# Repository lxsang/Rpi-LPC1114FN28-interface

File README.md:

# Rpi-LPC1114FN28-interface

This is a hobby project for an embedded application.  The point is that the Pi  is connected to a circuit based on the LPC1114FN28, in which, the ARM cortex M0 chip is used to collect sensor datas (IR sensor, sonar sensor, etc.) and control some motors using an IC controller. The Pi talks to the LPC1114FN28 via a serial connection (UART or SPI), and takes care of some high level calculations based on the datas provided by the LPC chip, it then can analyse the environment's context and send commands to the slave (ARM) chip for some control. For this prject, i decide to design my own PCB for the interface and write a firmware/middleware for  the interface.

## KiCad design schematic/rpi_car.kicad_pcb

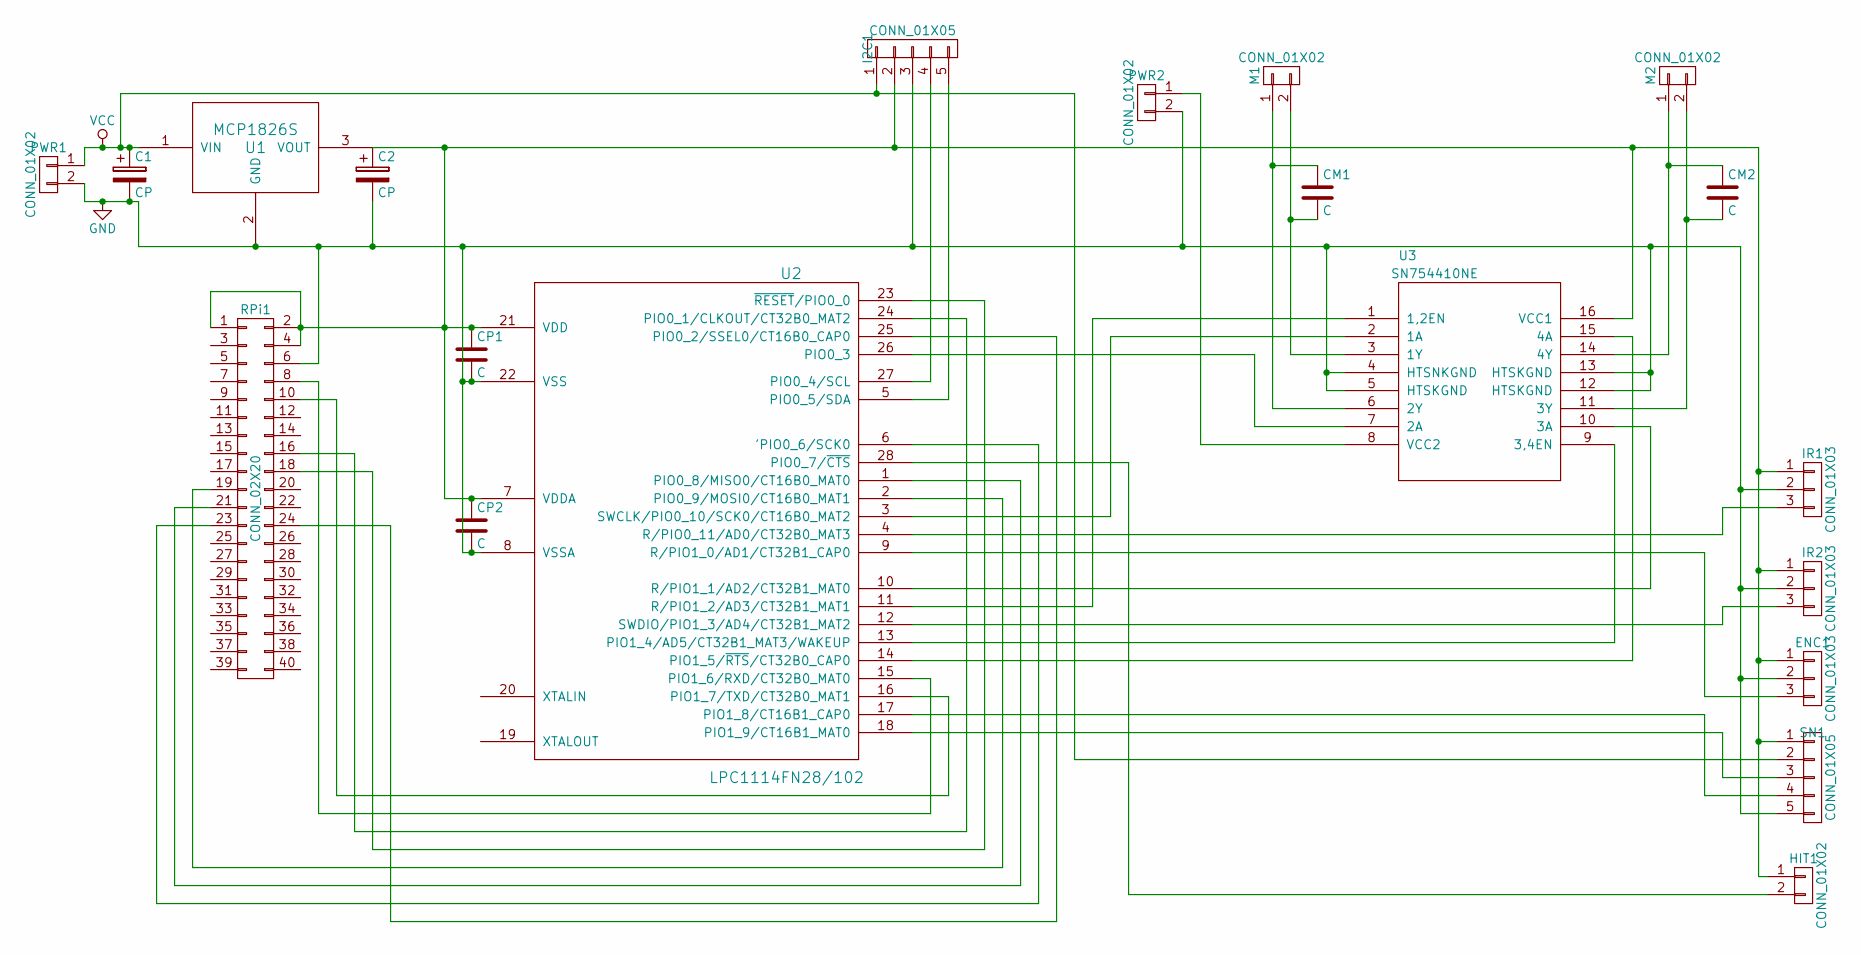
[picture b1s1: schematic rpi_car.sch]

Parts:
C1, C2: CP; CP_Radial_D4.0mm_P1.50mm
CM1, CM2: C; C_Rect_L4.0mm_W2.5mm_P2.50mm
CP1, CP2: C; C_Rect_L4.0mm_W2.5mm_P2.50mm
ENC1: CONN_01X03; Pin_Header_Straight_1x03
HIT1: CONN_01X02; Pin_Header_Straight_1x02
I2C1: CONN_01X05; Pin_Header_Straight_1x05
IR1, IR2: CONN_01X03; Pin_Header_Straight_1x03
M1, M2: CONN_01X02; Pin_Header_Straight_1x02
PWR1, PWR2: CONN_01X02; Pin_Header_Straight_1x02
RPi1: CONN_02X20; Pin_Header_Straight_2x20
SN1: CONN_01X05; Pin_Header_Straight_1x05
U1: MCP1826S; Pin_Header_Straight_1x03
U2: LPC1114FN28/102; DIP-28_W15.24mm
U3: SN754410NE; DIP-16_W7.62mm

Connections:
GND: C1.2, C2.2, CP1.2, CP2.2, ENC1.2, I2C1.3, IR1.2, IR2.2, PWR1.2, PWR2.2, RPi1.6, SN1.5, U1.2 (GND), U2.8 (VSSA), U2.22 (VSS), U3.4 (HTSNKGND), U3.5 (HTSKGND), U3.12 (HTSKGND), U3.13 (HTSKGND)
unnamed: C2.1, CP1.1, CP2.1, ENC1.1, HIT1.1, I2C1.2, IR1.1, IR2.1, RPi1.1, RPi1.2, RPi1.4, SN1.1, U1.3 (VOUT), U2.7 (VDDA), U2.21 (VDD), U3.16 (VCC1)
unnamed: CM1.1, M1.1, U3.6 (2Y)
unnamed: CM1.2, M1.2, U3.3 (1Y)
unnamed: CM2.1, M2.1, U3.14 (4Y)
unnamed: CM2.2, M2.2, U3.11 (3Y)
unnamed: ENC1.3, U2.9 (R/PIO1_0/AD1/CT32B1_CAP0)
unnamed: HIT1.2, U2.28 (PIO0_7/~CTS)
unnamed: I2C1.4, U2.27 (PIO0_4/SCL)
unnamed: I2C1.5, U2.5 (PIO0_5/SDA)
unnamed: IR1.3, U2.4 (R/PIO0_11/AD0/CT32B0_MAT3)
unnamed: IR2.3, U2.12 (SWDIO/PIO1_3/AD4/CT32B1_MAT2)
unnamed: PWR2.1, U3.8 (VCC2)
unnamed: RPi1.8, U2.15 (PIO1_6/RXD/CT32B0_MAT0)
unnamed: RPi1.10, U2.16 (PIO1_7/TXD/CT32B0_MAT1)
unnamed: RPi1.16, U2.24 (PIO0_1/CLKOUT/CT32B0_MAT2)
unnamed: RPi1.18, U2.23 (~RESET~/PIO0_0)
unnamed: RPi1.19, U2.2 (PIO0_9/MOSI0/CT16B0_MAT1)
unnamed: RPi1.21, U2.1 (PIO0_8/MISO0/CT16B0_MAT0)
unnamed: RPi1.23, U2.6 ('PIO0_6/SCK0)
unnamed: RPi1.24, U2.25 (PIO0_2/SSEL0/CT16B0_CAP0)
unnamed: SN1.3, U2.18 (PIO1_9/CT16B1_MAT0)
unnamed: SN1.4, U2.17 (PIO1_8/CT16B1_CAP0)
unnamed: U2.3 (SWCLK/PIO0_10/SCK0/CT16B0_MAT2), U3.2 (1A)
unnamed: U2.10 (R/PIO1_1/AD2/CT32B1_MAT0), U3.10 (3A)
unnamed: U2.11 (R/PIO1_2/AD3/CT32B1_MAT1), U3.1 (1,2EN)
unnamed: U2.13 (PIO1_4/AD5/CT32B1_MAT3/WAKEUP), U3.9 (3,4EN)
unnamed: U2.14 (PIO1_5/~RTS~/CT32B0_CAP0), U3.15 (4A)
unnamed: U2.26 (PIO0_3), U3.7 (2A)
VCC: C1.1, I2C1.1, PWR1.1, SN1.2, U1.1 (VIN)

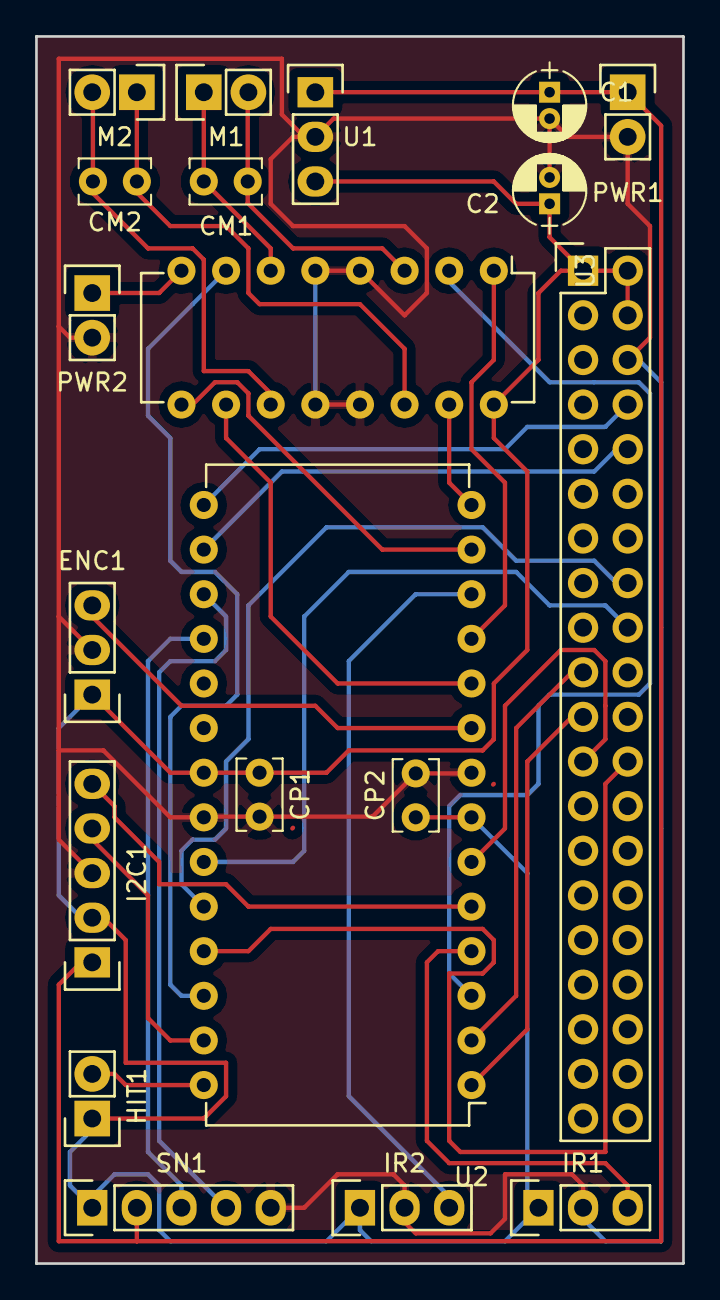
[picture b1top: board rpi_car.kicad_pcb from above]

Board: 2 copper layers, 36.8 x 69.8 mm, 20 parts (0 on the bottom side), 30 nets.

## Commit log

2018-02-27 commit schematic
2018-02-27 schematic
2018-03-07 Create Makefile
